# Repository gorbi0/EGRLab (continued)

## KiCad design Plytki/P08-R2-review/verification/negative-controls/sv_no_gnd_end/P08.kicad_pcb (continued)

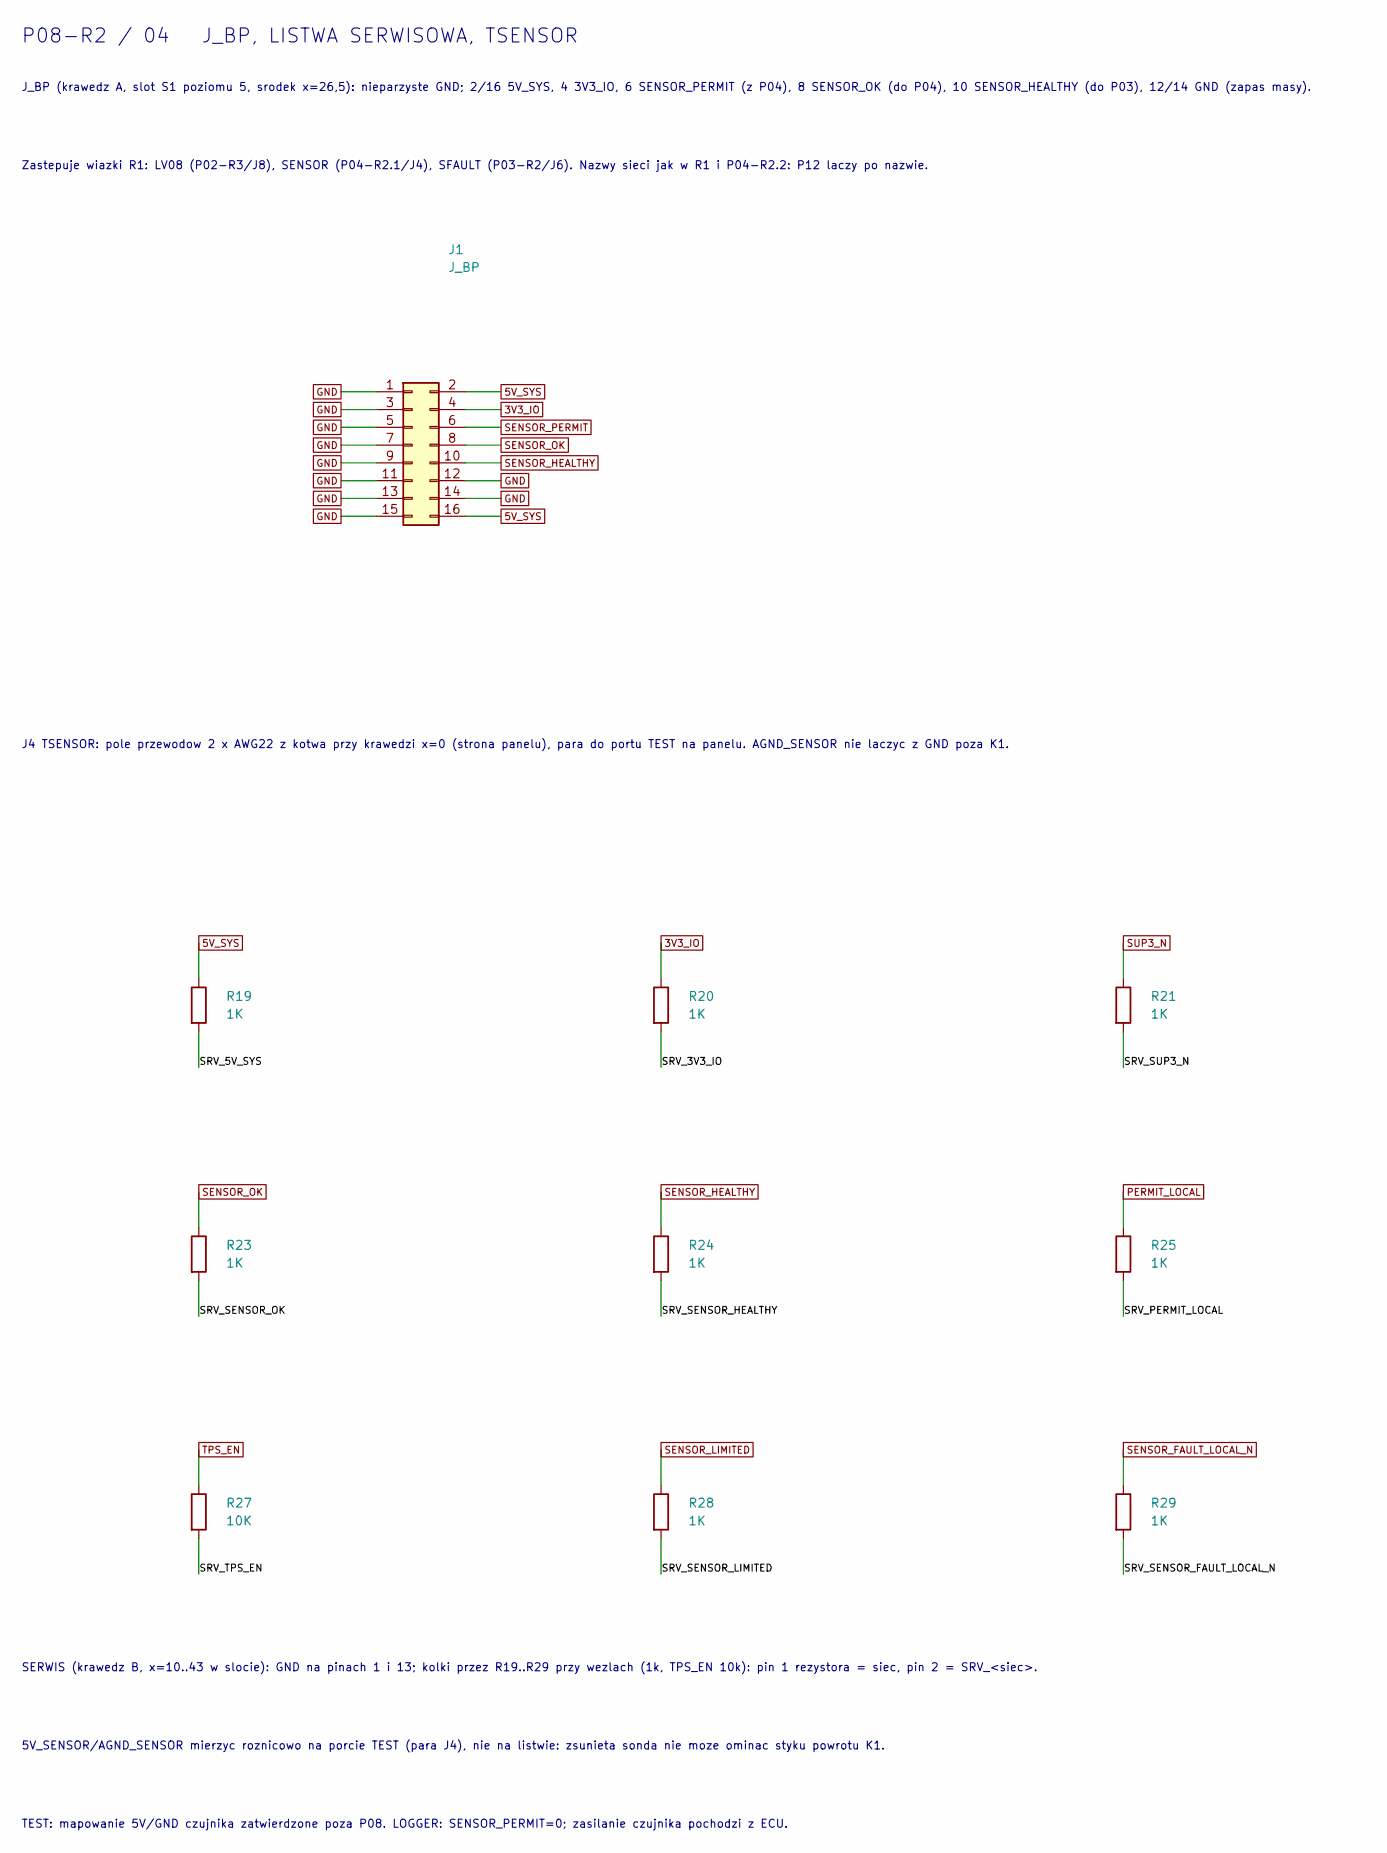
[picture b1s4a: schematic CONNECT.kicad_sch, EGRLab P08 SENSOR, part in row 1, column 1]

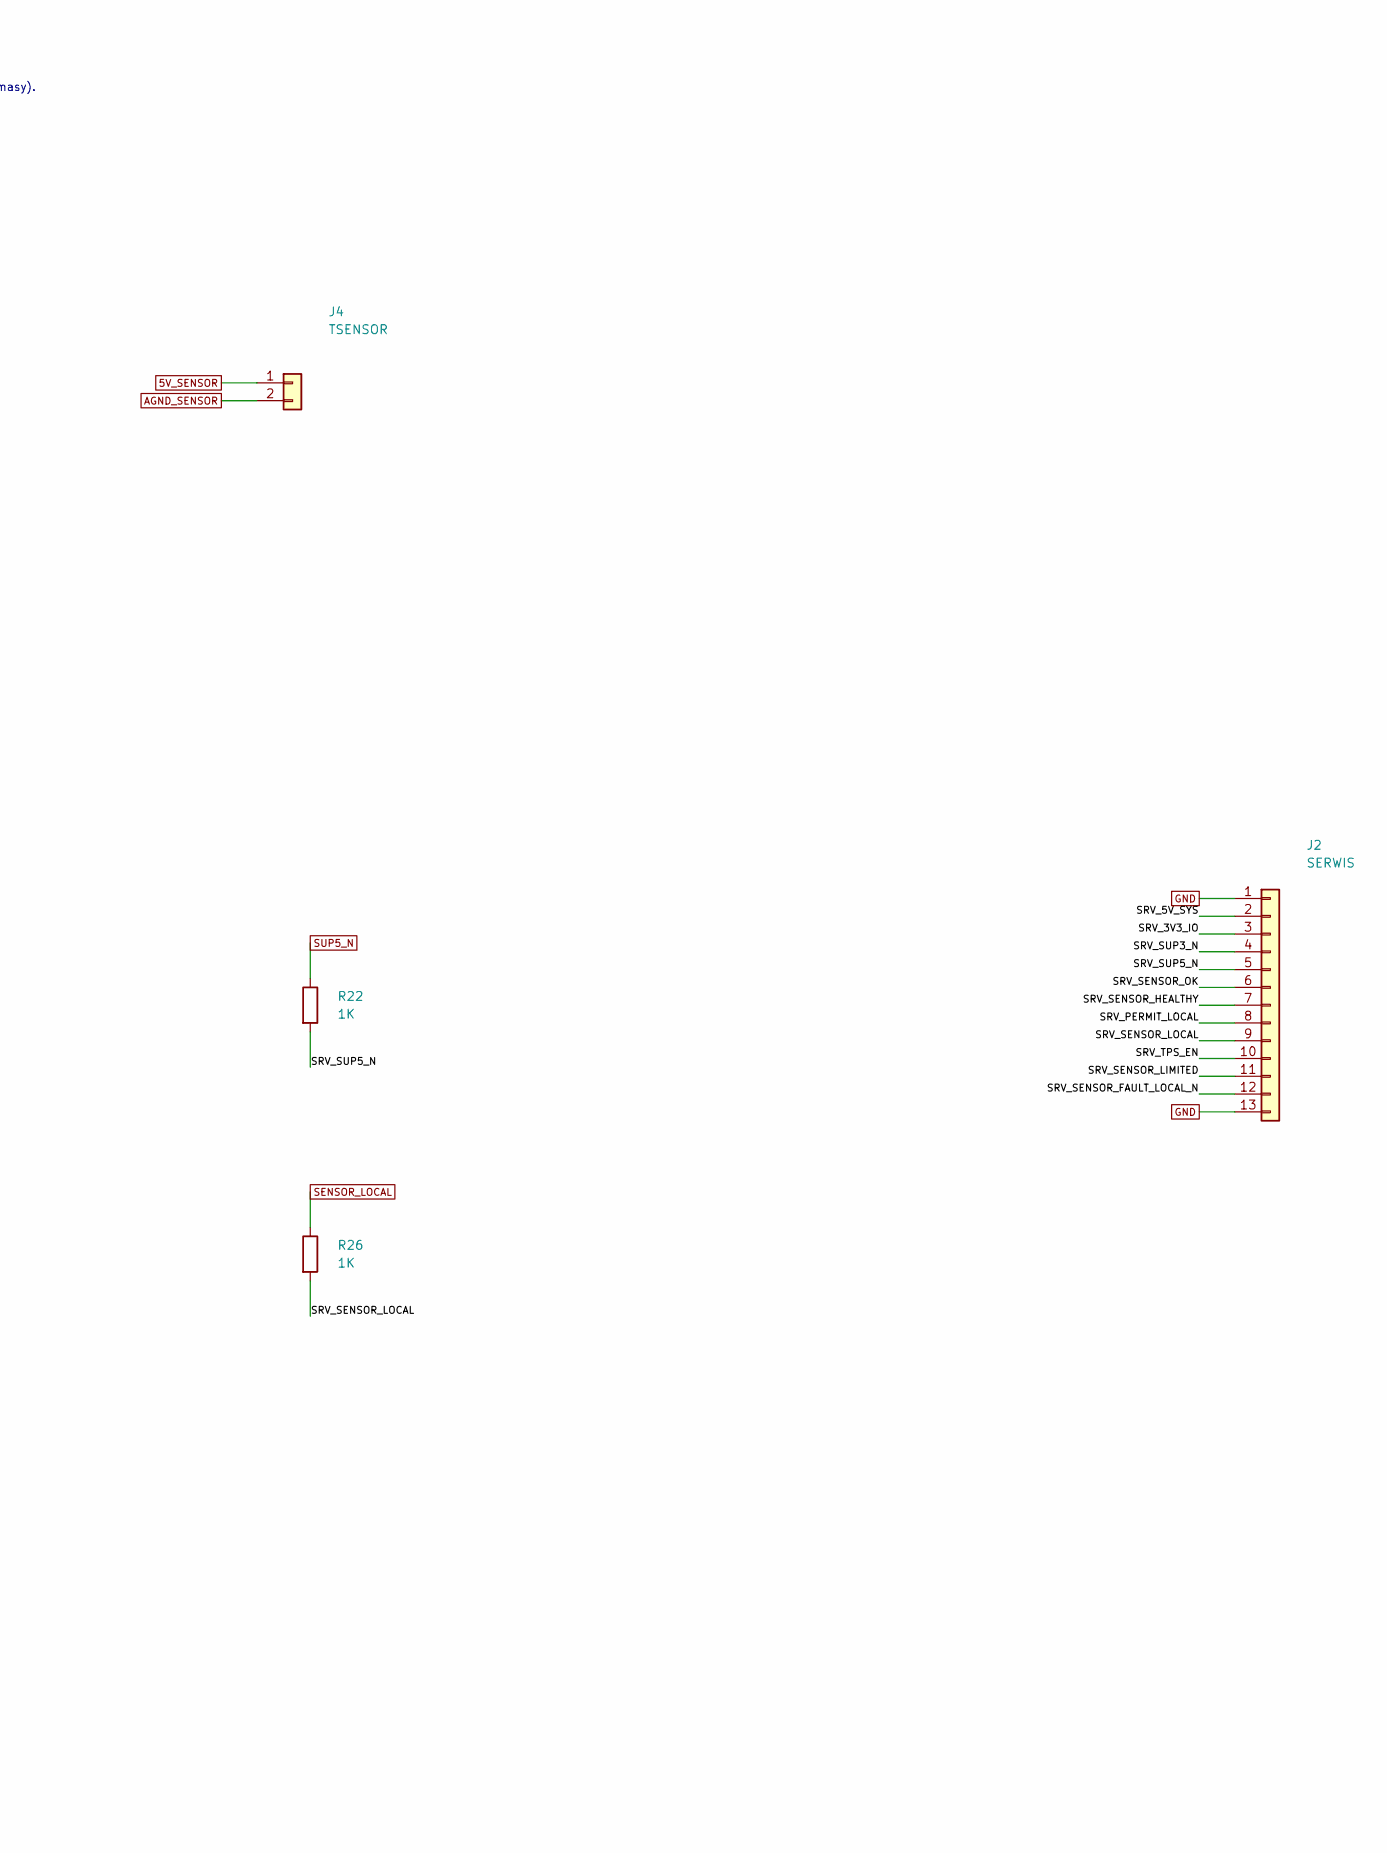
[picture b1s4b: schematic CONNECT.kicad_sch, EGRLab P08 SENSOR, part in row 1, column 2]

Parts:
J1: J_BP; IDC-Header_2x08_P2.54mm_Horizontal; MPN IDC header 2x8 2.54mm angled shrouded, 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
J2: SERWIS; PinHeader_1x13_P2.54mm_Horizontal; MPN Goldpin 1x13 2.54mm angled (buy angled 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
J4: TSENSOR; PTH_TSENSOR_2; MPN 2 x AWG22 soldered, tie anchor 12 mm
R19, R20, R21, R22, R23, R24, R25, R26, R28, R29: 1K; R_1206_3216Metric_Pad1.30x1.75mm_HandSolder; MPN SMD 1206 1% 0.25W 1K
R27: 10K; R_1206_3216Metric_Pad1.30x1.75mm_HandSolder; MPN SMD 1206 1% 0.25W 10K

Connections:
3V3_IO: J1.4, R20.1; also elsewhere on the board
5V_SENSOR: J4.1; also elsewhere on the board
5V_SYS: J1.2, J1.16, R19.1; also elsewhere on the board
/CONNECT/SRV_3V3_IO: J2.3, R20.2
/CONNECT/SRV_5V_SYS: J2.2, R19.2
/CONNECT/SRV_PERMIT_LOCAL: J2.8, R25.2
/CONNECT/SRV_SENSOR_HEALTHY: J2.7, R24.2
/CONNECT/SRV_SENSOR_LIMITED: J2.11, R28.2
/CONNECT/SRV_SENSOR_LOCAL: J2.9, R26.2
/CONNECT/SRV_SENSOR_OK: J2.6, R23.2
/CONNECT/SRV_SUP3_N: J2.4, R21.2
/CONNECT/SRV_SUP5_N: J2.5, R22.2
/CONNECT/SRV_TPS_EN: J2.10, R27.2
AGND_SENSOR: J4.2; also elsewhere on the board
PERMIT_LOCAL: R25.1; also elsewhere on the board
SENSOR_FAULT_LOCAL_N: R29.1; also elsewhere on the board
SENSOR_HEALTHY: J1.10, R24.1; also elsewhere on the board
SENSOR_LIMITED: R28.1; also elsewhere on the board
SENSOR_LOCAL: R26.1; also elsewhere on the board
SENSOR_OK: J1.8, R23.1; also elsewhere on the board
SENSOR_PERMIT: J1.6; also elsewhere on the board
SUP3_N: R21.1; also elsewhere on the board
SUP5_N: R22.1; also elsewhere on the board
TPS_EN: R27.1; also elsewhere on the board

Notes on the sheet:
J_BP (krawedz A, slot S1 poziomu 5, srodek x=26,5): nieparzyste GND; 2/16 5V_SYS, 4 3V3_IO, 6 SENSOR_PERMIT (z P04), 8 SENSOR_OK (do P04), 10 SENSOR_HEALTHY (do P03), 12/14 GND (zapas masy).
Zastepuje wiazki R1: LV08 (P02-R3/J8), SENSOR (P04-R2.1/J4), SFAULT (P03-R2/J6). Nazwy sieci jak w R1 i P04-R2.2: P12 laczy po nazwie.
J4 TSENSOR: pole przewodow 2 x AWG22 z kotwa przy krawedzi x=0 (strona panelu), para do portu TEST na panelu. AGND_SENSOR nie laczyc z GND poza K1.
SERWIS (krawedz B, x=10..43 w slocie): GND na pinach 1 i 13; kolki przez R19..R29 przy wezlach (1k, TPS_EN 10k): pin 1 rezystora = siec, pin 2 = SRV_<siec>.
5V_SENSOR/AGND_SENSOR mierzyc roznicowo na porcie TEST (para J4), nie na listwie: zsunieta sonda nie moze ominac styku powrotu K1.
TEST: mapowanie 5V/GND czujnika zatwierdzone poza P08. LOGGER: SENSOR_PERMIT=0; zasilanie czujnika pochodzi z ECU.
P08-R2 / 04 J_BP, LISTWA SERWISOWA, TSENSOR

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
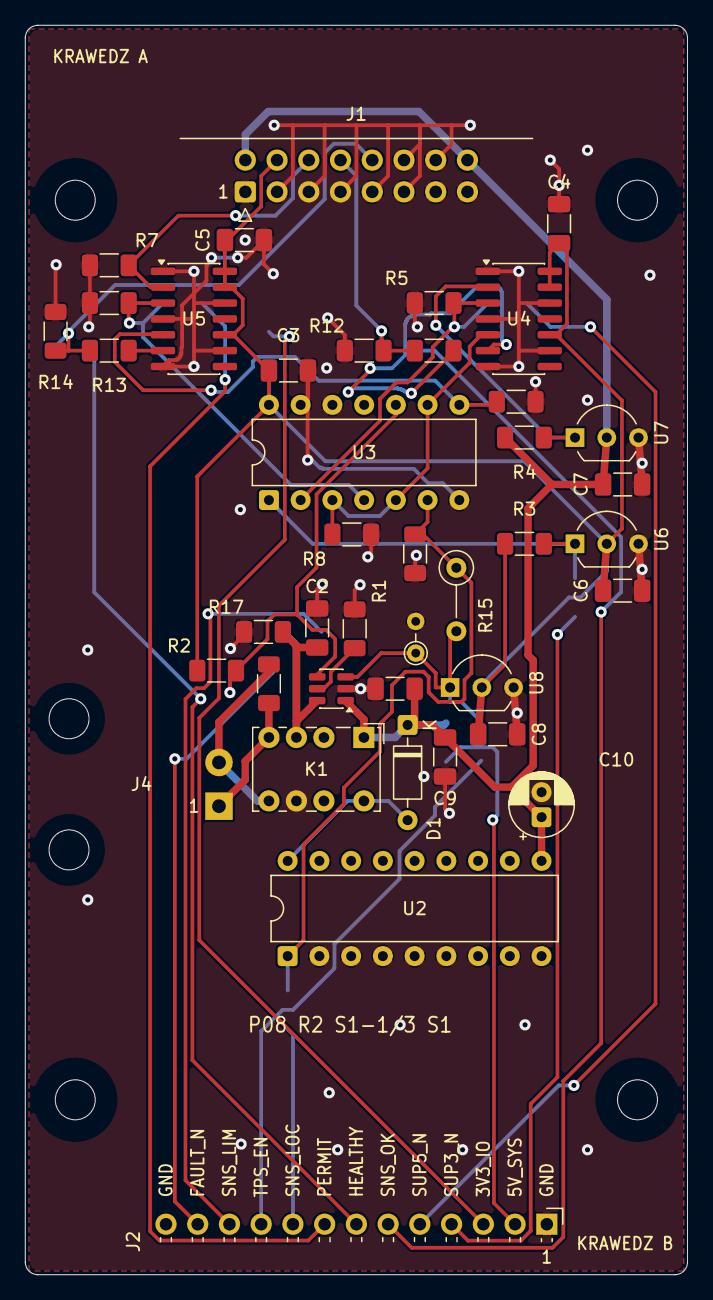
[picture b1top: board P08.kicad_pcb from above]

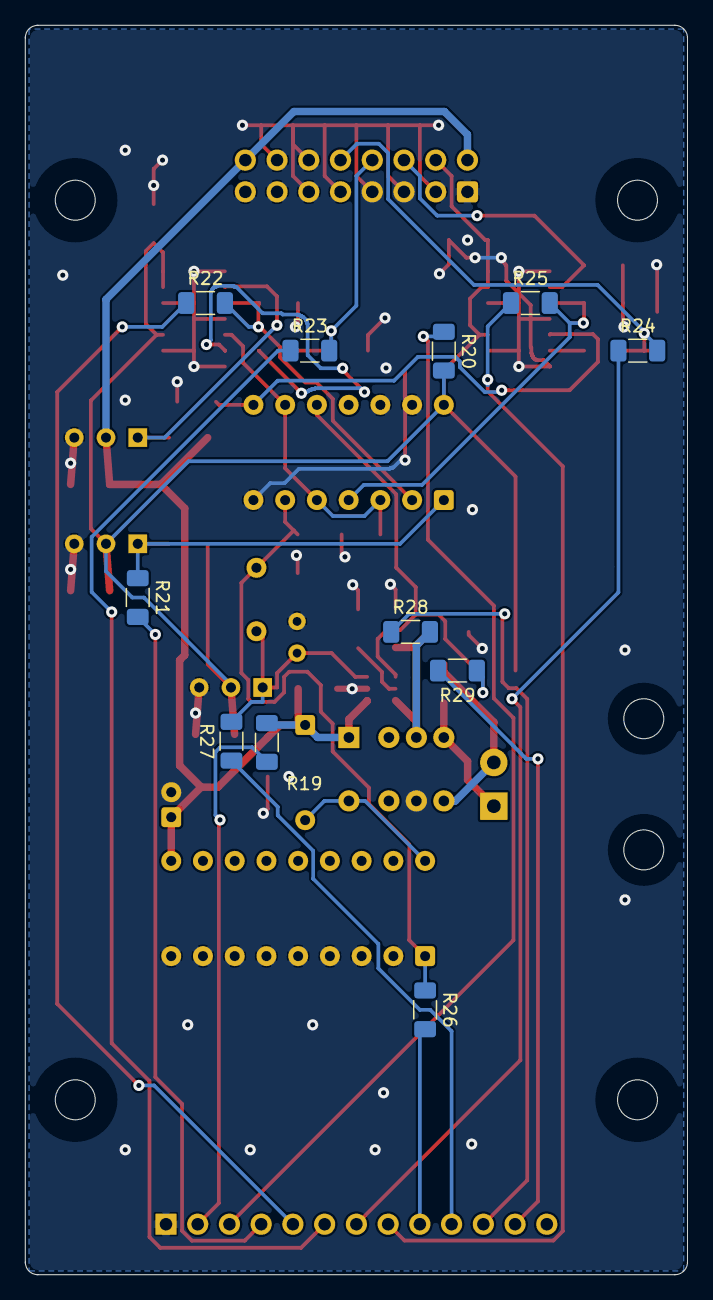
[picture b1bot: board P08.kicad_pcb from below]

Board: 2 copper layers, 53.0 x 100.0 mm, 56 parts (11 on the bottom side), 33 nets.

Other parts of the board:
H1, H2, H3, H4: M3 NPTH

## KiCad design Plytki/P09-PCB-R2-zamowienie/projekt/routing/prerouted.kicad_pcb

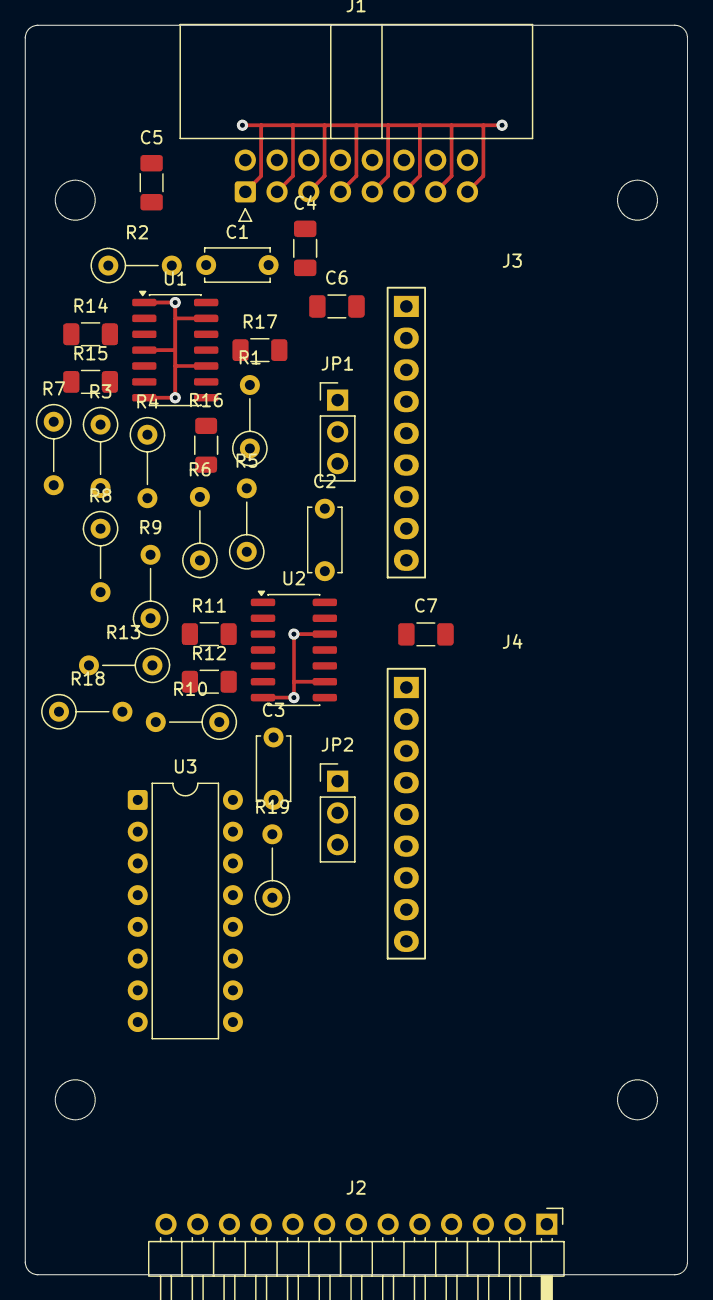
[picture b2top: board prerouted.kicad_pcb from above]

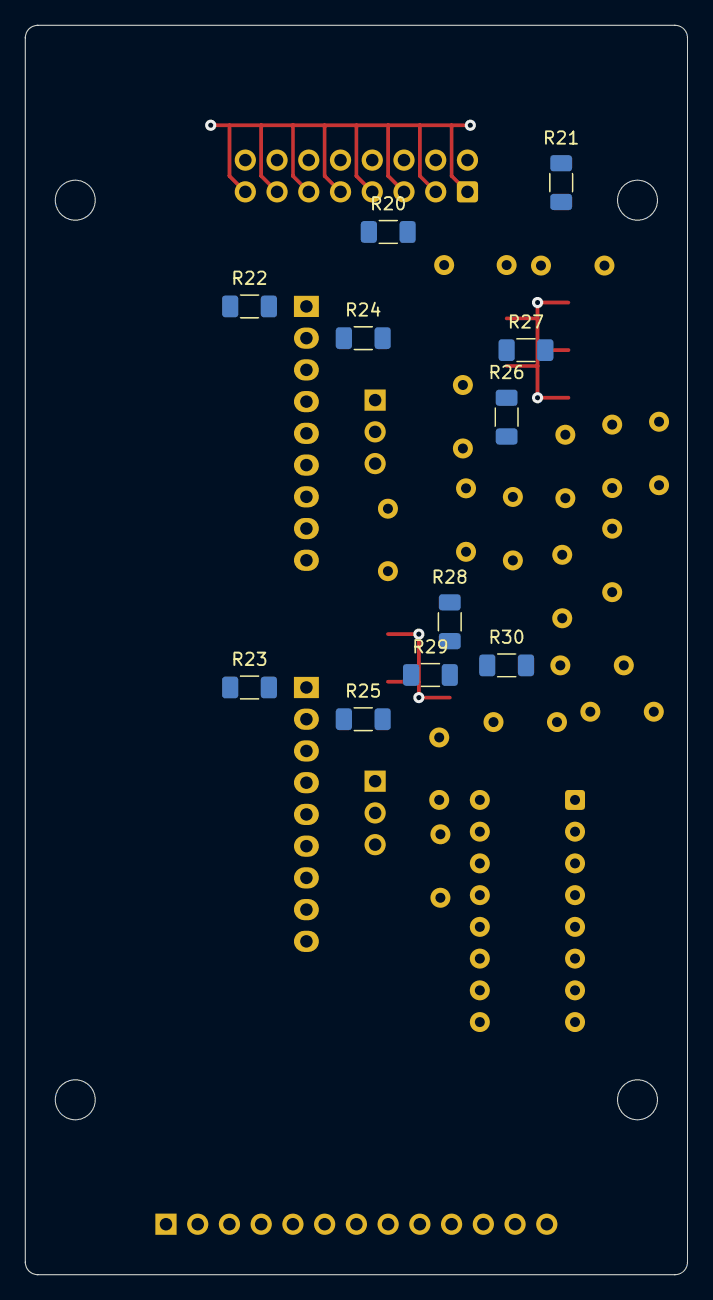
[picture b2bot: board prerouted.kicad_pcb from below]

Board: 2 copper layers, 53.0 x 100.0 mm, 50 parts (11 on the bottom side), 37 nets.

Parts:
C1, C2, C3: 100n; C_Disc_D5.0mm_W2.5mm_P5.00mm
C4, C5: 4u7; C_1206_3216Metric_Pad1.33x1.80mm_HandSolder
C6, C7: 1u; C_1206_3216Metric_Pad1.33x1.80mm_HandSolder
H1, H2, H3, H4: M3 NPTH
J1: J_BP; IDC-Header_2x08_P2.54mm_Horizontal
J2: SERWIS; PinHeader_1x13_P2.54mm_Horizontal
J3: TC1; MAX31856_XU
J4: TC2; MAX31856_XU
JP1, JP2: VIN SELECT; PinHeader_1x03_P2.54mm_Vertical
R1, R2, R5, R6, R18, R19: 10K; R_Axial_DIN0207_L6.3mm_D2.5mm_P5.08mm_Vertical
R3, R4, R7, R8, R9, R10, R13: 100K; R_Axial_DIN0207_L6.3mm_D2.5mm_P5.08mm_Vertical
R11, R12: 100R; R_1206_3216Metric_Pad1.30x1.75mm_HandSolder
R14, R15, R16, R17: 47R; R_1206_3216Metric_Pad1.30x1.75mm_HandSolder
R20, R21, R22, R23, R24, R25, R26, R27, R28, R29, R30: 1K; R_1206_3216Metric_Pad1.30x1.75mm_HandSolder
U1, U2: 74LVC125AD; SOIC-14_3.9x8.7mm_P1.27mm
U3: SN74HC139N; DIP-16_W7.62mm

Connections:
3V3_IO: C1.1, C2.1, C3.1, C4.1, J1.4, JP1.1, JP2.1, R1.1, R2.1, R5.1, R6.1, R18.1, R19.1, R20.1, U1.14, U2.10, U2.13, U2.14, U3.15, U3.16
5V_SYS: C5.1, J1.2, J1.16, JP1.3, JP2.3, R21.1
/CONNECT/SRV_3V3_IO: J2.2, R20.2
/CONNECT/SRV_5V_SYS: J2.3, R21.2
/CONNECT/SRV_CS1_BUF: J2.8, R26.2
/CONNECT/SRV_CS2_BUF: J2.9, R27.2
/CONNECT/SRV_OE1_N: J2.10, R28.2
/CONNECT/SRV_OE2_N: J2.11, R29.2
/CONNECT/SRV_SPI3_MISO: J2.12, R30.2
/CONNECT/SRV_TC1_3VO: J2.6, R24.2
/CONNECT/SRV_TC1_VIN: J2.4, R22.2
/CONNECT/SRV_TC2_3VO: J2.7, R25.2
/CONNECT/SRV_TC2_VIN: J2.5, R23.2
/SELECT/TX1: R11.1, U2.3
/SELECT/TX2: R12.1, U2.6
/SPI/CLK_BUF: R7.1, R14.1, U1.3
/SPI/MOSI_BUF: R8.1, R15.1, U1.6
CLK_MODULE: J3.4, J4.4, R14.2
CS1_BUF: R5.2, R16.1, R26.1, U1.8, U3.2
CS2_BUF: R6.2, R17.1, R27.1, U1.11, U3.3
GND: C1.2, C2.2, C3.2, C4.2, C5.2, C6.2, C7.2, J1.1, J1.3, J1.5, J1.7, J1.9, J1.11, J1.13, J1.15, J2.1, J2.13, J3.3, J4.3, R3.2, R4.2, R7.2, R8.2, R9.2, R10.2, R13.2, U1.1, U1.4, U1.7, U1.10, U1.13, U2.7, U2.9, U2.12, U3.1, U3.8, U3.13, U3.14
MOSI_MODULE: J3.6, J4.6, R15.2
OE1_N: R18.2, R28.1, U2.1, U3.6
OE2_N: R19.2, R29.1, U2.4, U3.5
SPI3_MISO: J1.10, R11.2, R12.2, R13.1, R30.1
SPI3_MOSI: J1.8, R4.1, U1.5
SPI3_SCLK: J1.6, R3.1, U1.2
TC1_3VO: J3.2, R24.1
TC1_CS: J1.12, R1.2, U1.9
TC1_CS_MODULE: J3.7, R16.2
TC1_MISO: J3.5, R9.1, U2.2
TC1_VIN: C6.1, J3.1, JP1.2, R22.1
TC2_3VO: J4.2, R25.1
TC2_CS: J1.14, R2.2, U1.12
TC2_CS_MODULE: J4.7, R17.2
TC2_MISO: J4.5, R10.1, U2.5
TC2_VIN: C7.1, J4.1, JP2.2, R23.1

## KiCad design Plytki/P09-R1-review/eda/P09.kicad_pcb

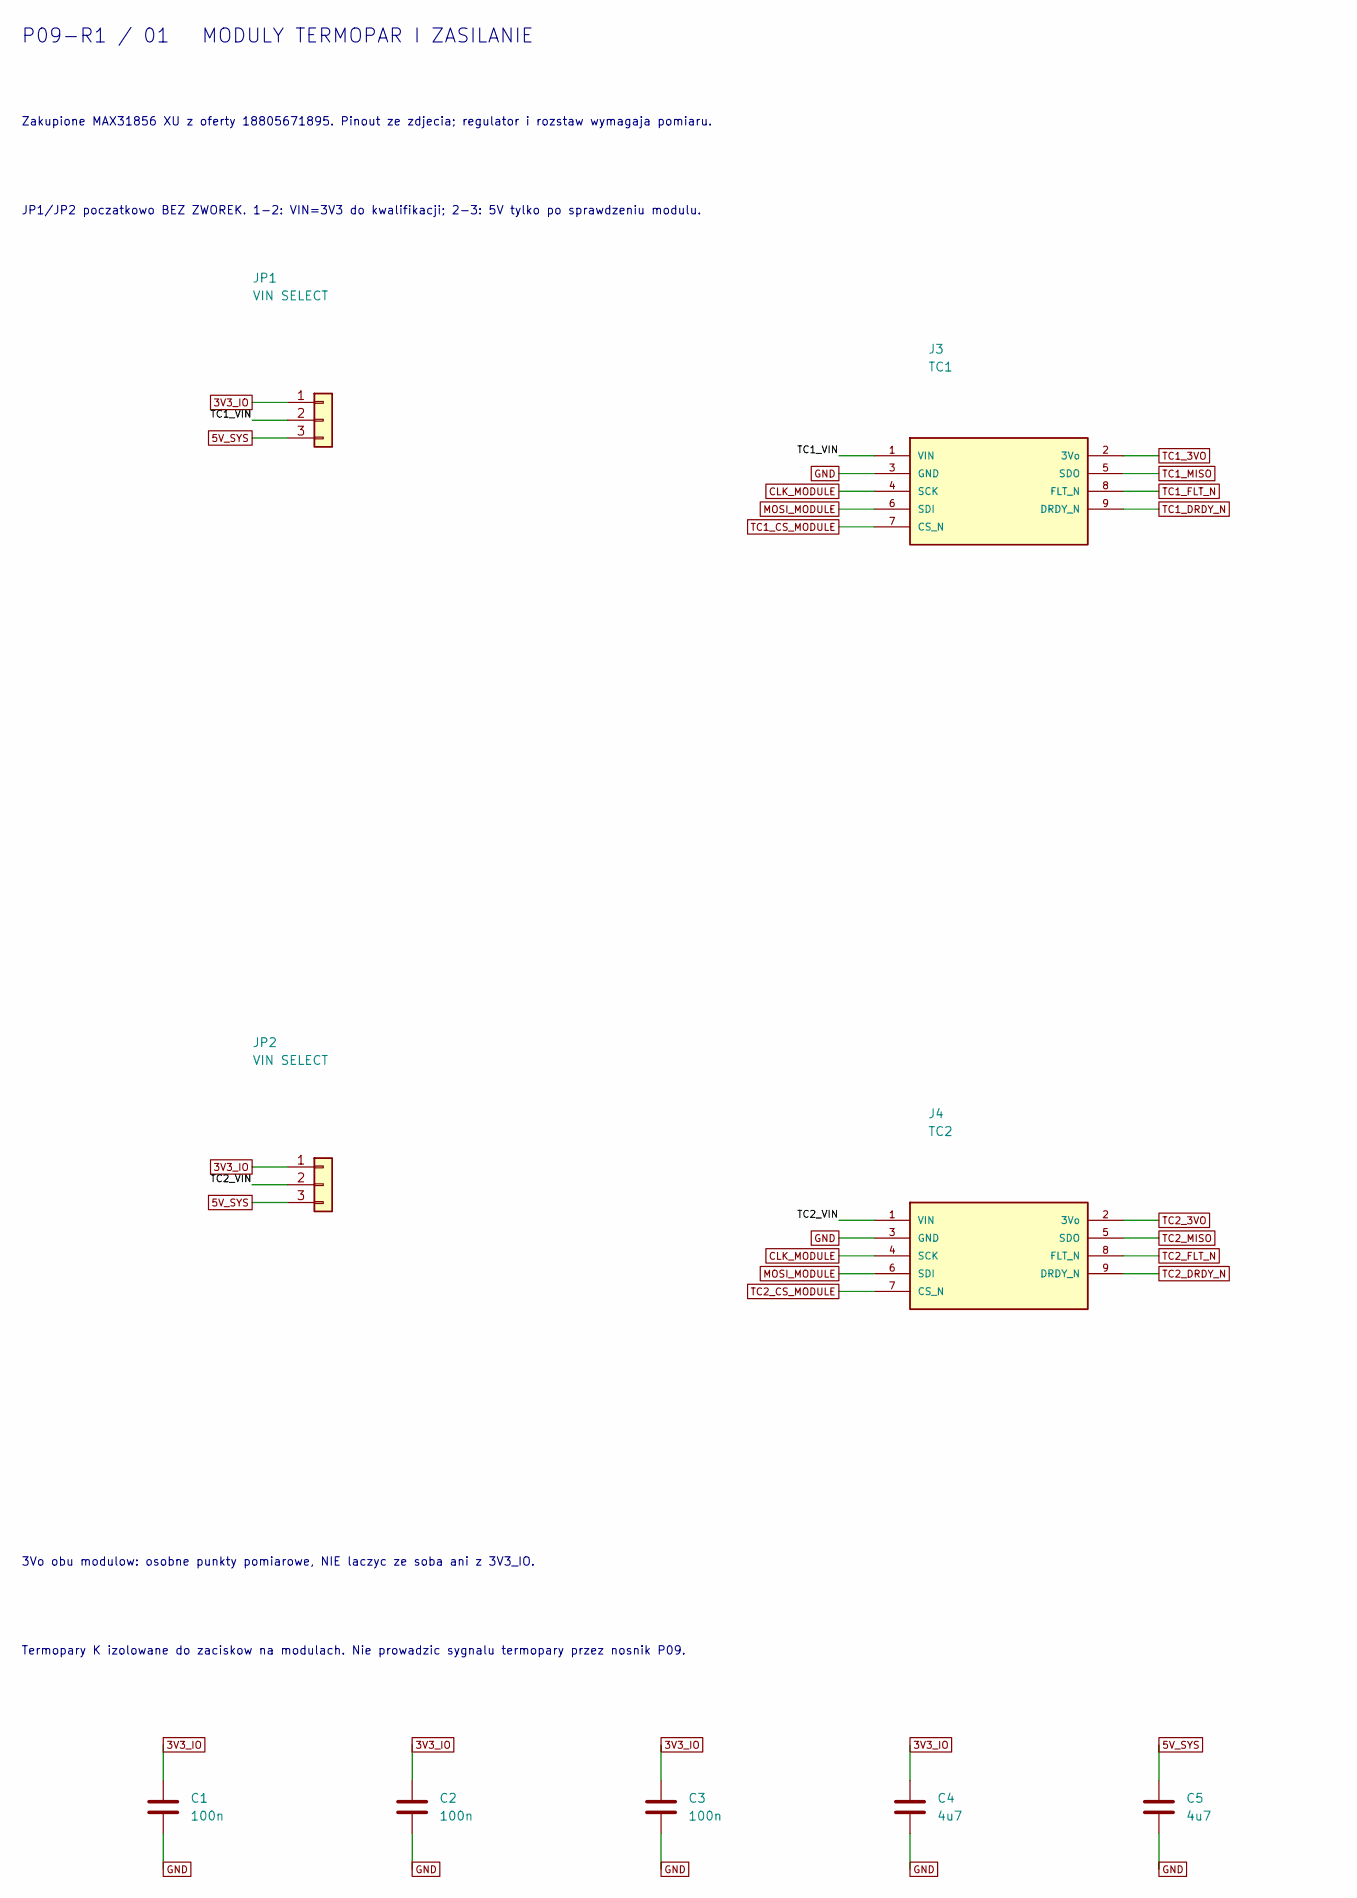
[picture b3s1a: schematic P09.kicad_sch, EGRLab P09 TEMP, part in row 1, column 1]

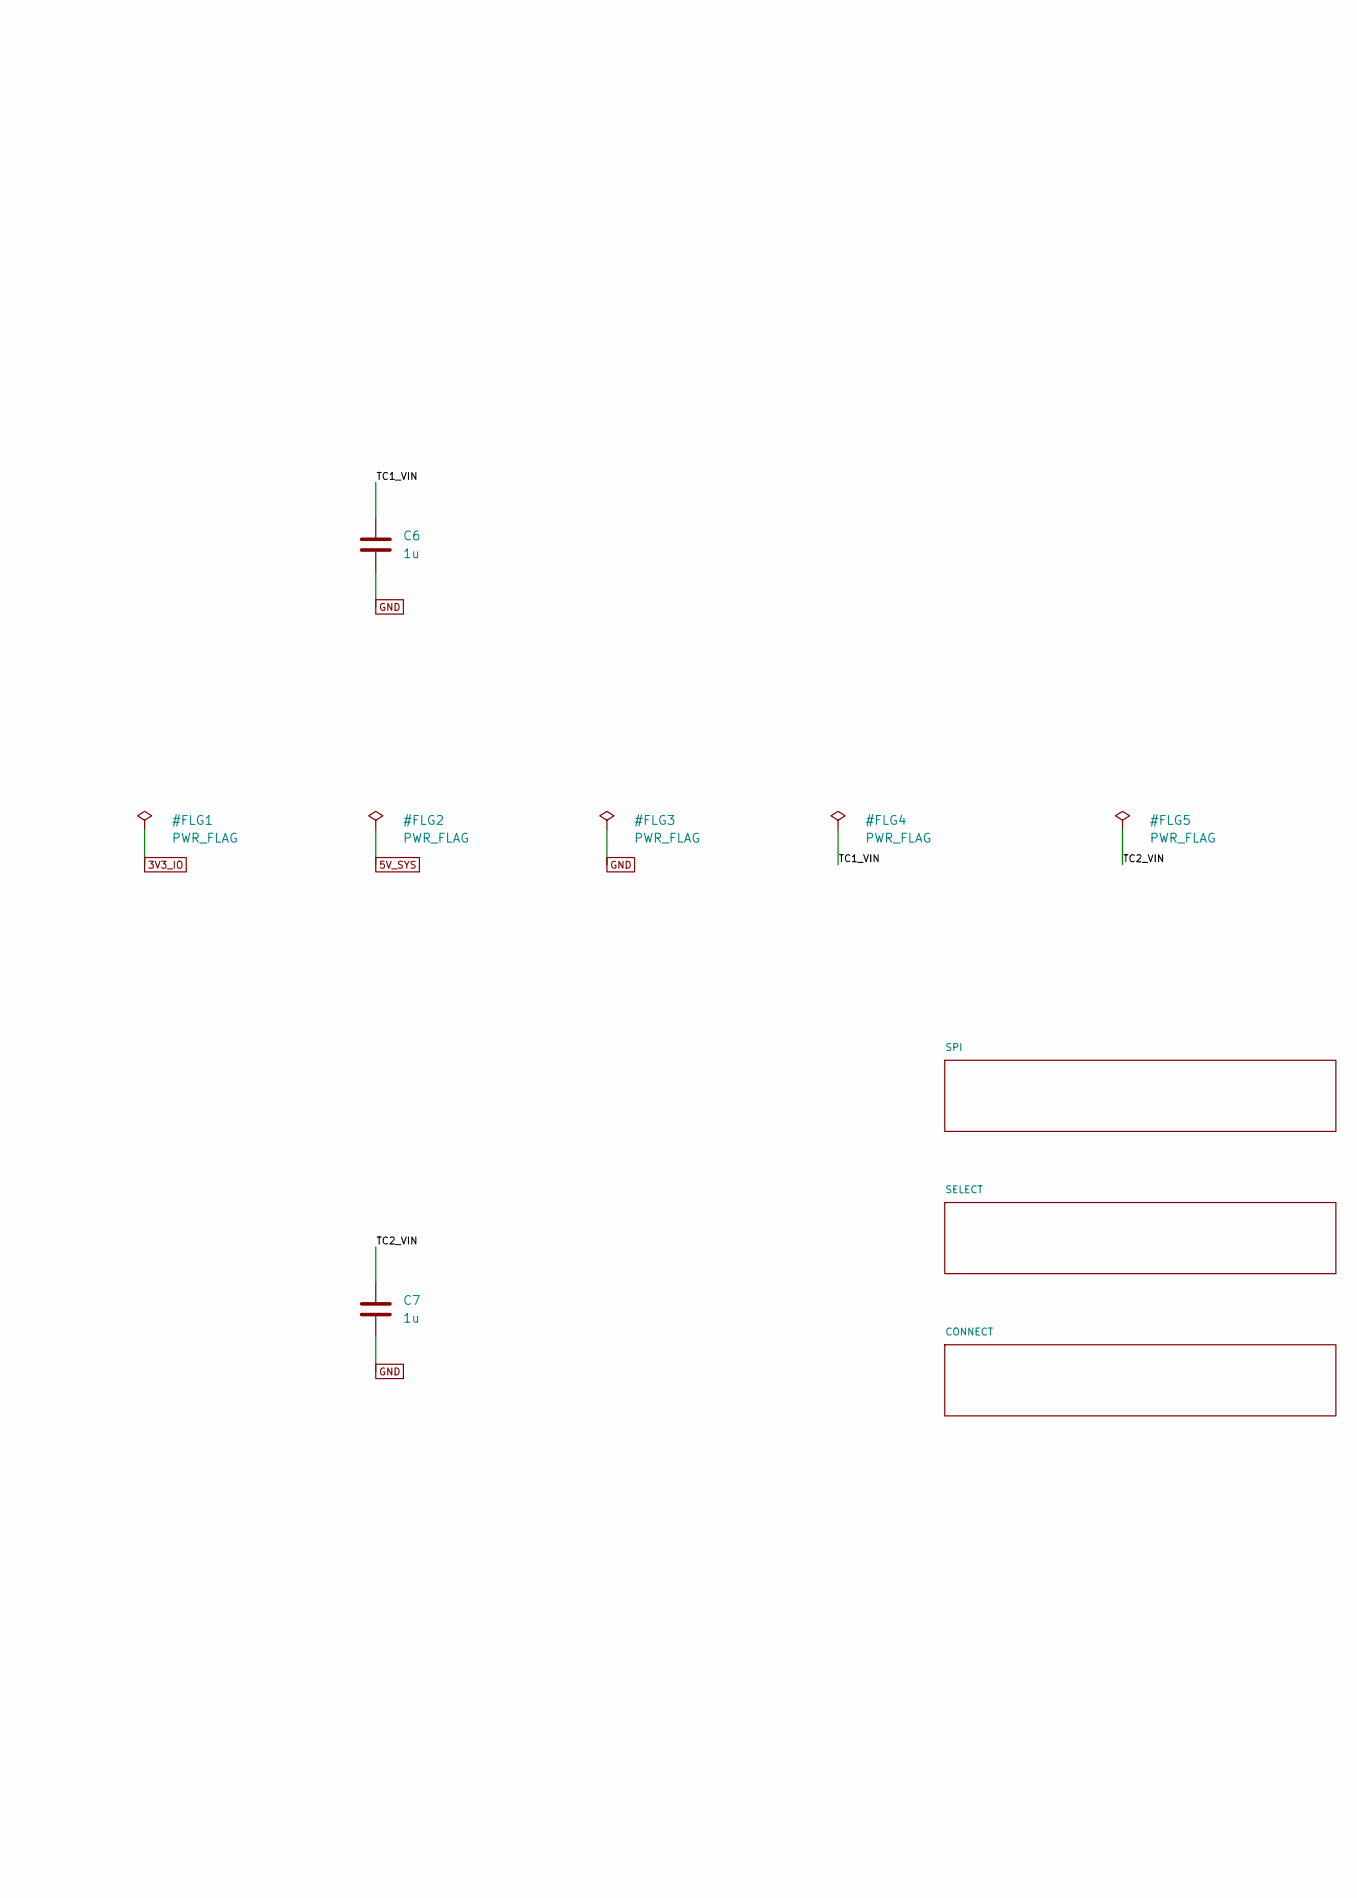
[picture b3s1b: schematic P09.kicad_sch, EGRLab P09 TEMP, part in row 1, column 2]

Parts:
C1, C2, C3: 100n; C_0805_2012Metric; MPN X7R 25V 10% 0805 100n
C4, C5: 4u7; C_0805_2012Metric; MPN X7R 25V 10% 0805 4u7
C6, C7: 1u; C_0805_2012Metric; MPN X7R 25V 10% 0805 1u
J3: TC1; MAX31856_XU_socket; MPN Socket 1x9 2.54mm Au + owned MAX31856 m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
J4: TC2; MAX31856_XU_socket; MPN Socket 1x9 2.54mm Au + owned MAX31856 m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
JP1, JP2: VIN SELECT; PinHeader_1x03_P2.54mm_Vertical; MPN Header 1x3 + one shunt (not fitted init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

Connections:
3V3_IO: C1.1, C2.1, C3.1, C4.1, JP1.1, JP2.1; also elsewhere on the board
5V_SYS: C5.1, JP1.3, JP2.3; also elsewhere on the board
/TC1_VIN: C6.1, J3.1 (VIN), JP1.2
/TC2_VIN: C7.1, J4.1 (VIN), JP2.2
CLK_MODULE: J3.4 (SCK), J4.4 (SCK); also elsewhere on the board
GND: C1.2, C2.2, C3.2, C4.2, C5.2, C6.2, C7.2, J3.3 (GND), J4.3 (GND); also elsewhere on the board
MOSI_MODULE: J3.6 (SDI), J4.6 (SDI); also elsewhere on the board
TC1_3VO: J3.2 (3Vo); also elsewhere on the board
TC1_CS_MODULE: J3.7 (CS_N); also elsewhere on the board
TC1_DRDY_N: J3.9 (DRDY_N); also elsewhere on the board
TC1_FLT_N: J3.8 (FLT_N); also elsewhere on the board
TC1_MISO: J3.5 (SDO); also elsewhere on the board
TC2_3VO: J4.2 (3Vo); also elsewhere on the board
TC2_CS_MODULE: J4.7 (CS_N); also elsewhere on the board
TC2_DRDY_N: J4.9 (DRDY_N); also elsewhere on the board
TC2_FLT_N: J4.8 (FLT_N); also elsewhere on the board
TC2_MISO: J4.5 (SDO); also elsewhere on the board

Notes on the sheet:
Zakupione MAX31856 XU z oferty 18805671895. Pinout ze zdjecia; regulator i rozstaw wymagaja pomiaru.
JP1/JP2 poczatkowo BEZ ZWOREK. 1-2: VIN=3V3 do kwalifikacji; 2-3: 5V tylko po sprawdzeniu modulu.
3Vo obu modulow: osobne punkty pomiarowe, NIE laczyc ze soba ani z 3V3_IO.
Termopary K izolowane do zaciskow na modulach. Nie prowadzic sygnalu termopary przez nosnik P09.
P09-R1 / 01 MODULY TERMOPAR I ZASILANIE
